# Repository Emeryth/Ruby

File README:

My implementation of the famous Ruby 9V battery Guitar amp by Runoffgroove [http://www.runoffgroove.com/ruby.html] with some modifications inspired by ElectroSmash 1Wamp [https://www.electrosmash.com/1wamp]

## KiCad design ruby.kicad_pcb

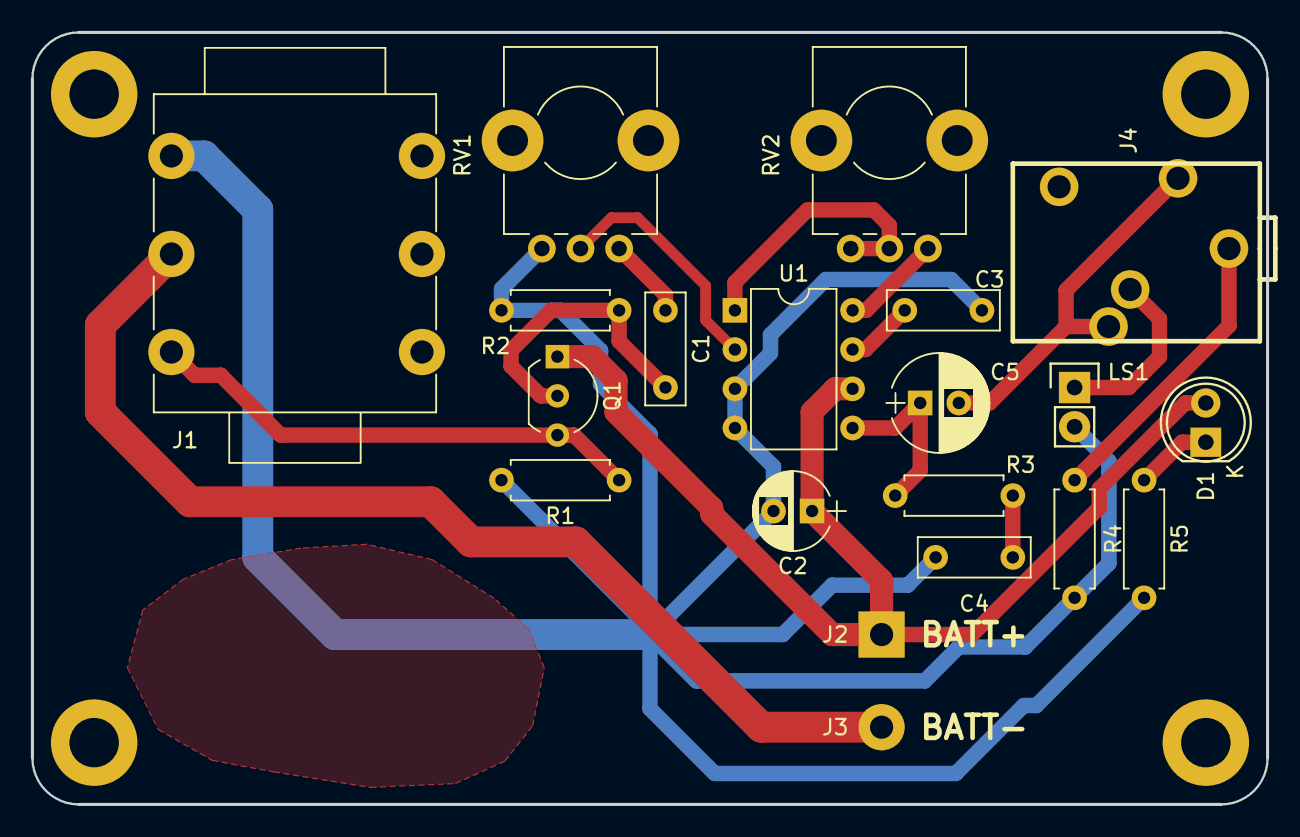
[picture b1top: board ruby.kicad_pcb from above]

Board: 2 copper layers, 80.0 x 50.0 mm, 20 parts (0 on the bottom side), 16 nets.

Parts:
C1, C4: 47n; C_Rect_L7.2mm_W2.5mm_P5.00mm_FKS2_FKP2_MKS2_MKP2
C2: 100u; CP_Radial_D5.0mm_P2.50mm
C3: 100n; C_Rect_L7.2mm_W2.5mm_P5.00mm_FKS2_FKP2_MKS2_MKP2
C5: 220u; CP_Radial_D6.3mm_P2.50mm
D1: LED; LED-5MM
J1: INPUT JACK; NMJ6HCD2
J2: BATT+; Measurement_Point_Square-TH_Big
J3: BATT-; Measurement_Point_Round-TH_Big
J4: HEADPHONE JACK; jack3.5-stereo-5
LS1: Speaker; Pin_Header_Straight_1x02
Q1: MPF102; TO-92_Inline_Wide
R1: 1M5; R_Axial_DIN0207_L6.3mm_D2.5mm_P7.62mm_Horizontal
R2: 3k9; R_Axial_DIN0207_L6.3mm_D2.5mm_P7.62mm_Horizontal
R3: 10; R_Axial_DIN0207_L6.3mm_D2.5mm_P7.62mm_Horizontal
R4: 1k; R_Axial_DIN0207_L6.3mm_D2.5mm_P7.62mm_Horizontal
R5: 6k8; R_Axial_DIN0207_L6.3mm_D2.5mm_P7.62mm_Horizontal
RV1: 10k-B; Potentiometer_Alps_RK09K_Horizontal
RV2: 1k; Potentiometer_Alps_RK09K_Horizontal
U1: LM386; DIP-8_W7.62mm

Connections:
+BATT: C2.1, D1.2, J2.1, Q1.1, U1.6
-BATT: J1.2, J3.1
/INPUT: J1.1, Q1.3, R1.1
/OUTPUT: C5.2, J4.1, J4.2
GND: C2.2, C3.1, C4.2, J1.3, LS1.2, R1.2, R2.2, R4.2, R5.2, RV1.3, U1.3, U1.4
unnamed: C1.1, RV1.1
unnamed: C1.2, Q1.2, R2.1
unnamed: C3.2, U1.7
unnamed: C4.1, R3.2
unnamed: C5.1, R3.1, U1.5
unnamed: D1.1, R5.1
unnamed: J4.3, R4.1
unnamed: J4.4, LS1.1
unnamed: RV1.2, U1.2
unnamed: RV2.1, U1.8
unnamed: RV2.2, RV2.3, U1.1

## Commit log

2018-01-15 Migrate to new eeschema format
2018-01-15 Add readme and pictures
